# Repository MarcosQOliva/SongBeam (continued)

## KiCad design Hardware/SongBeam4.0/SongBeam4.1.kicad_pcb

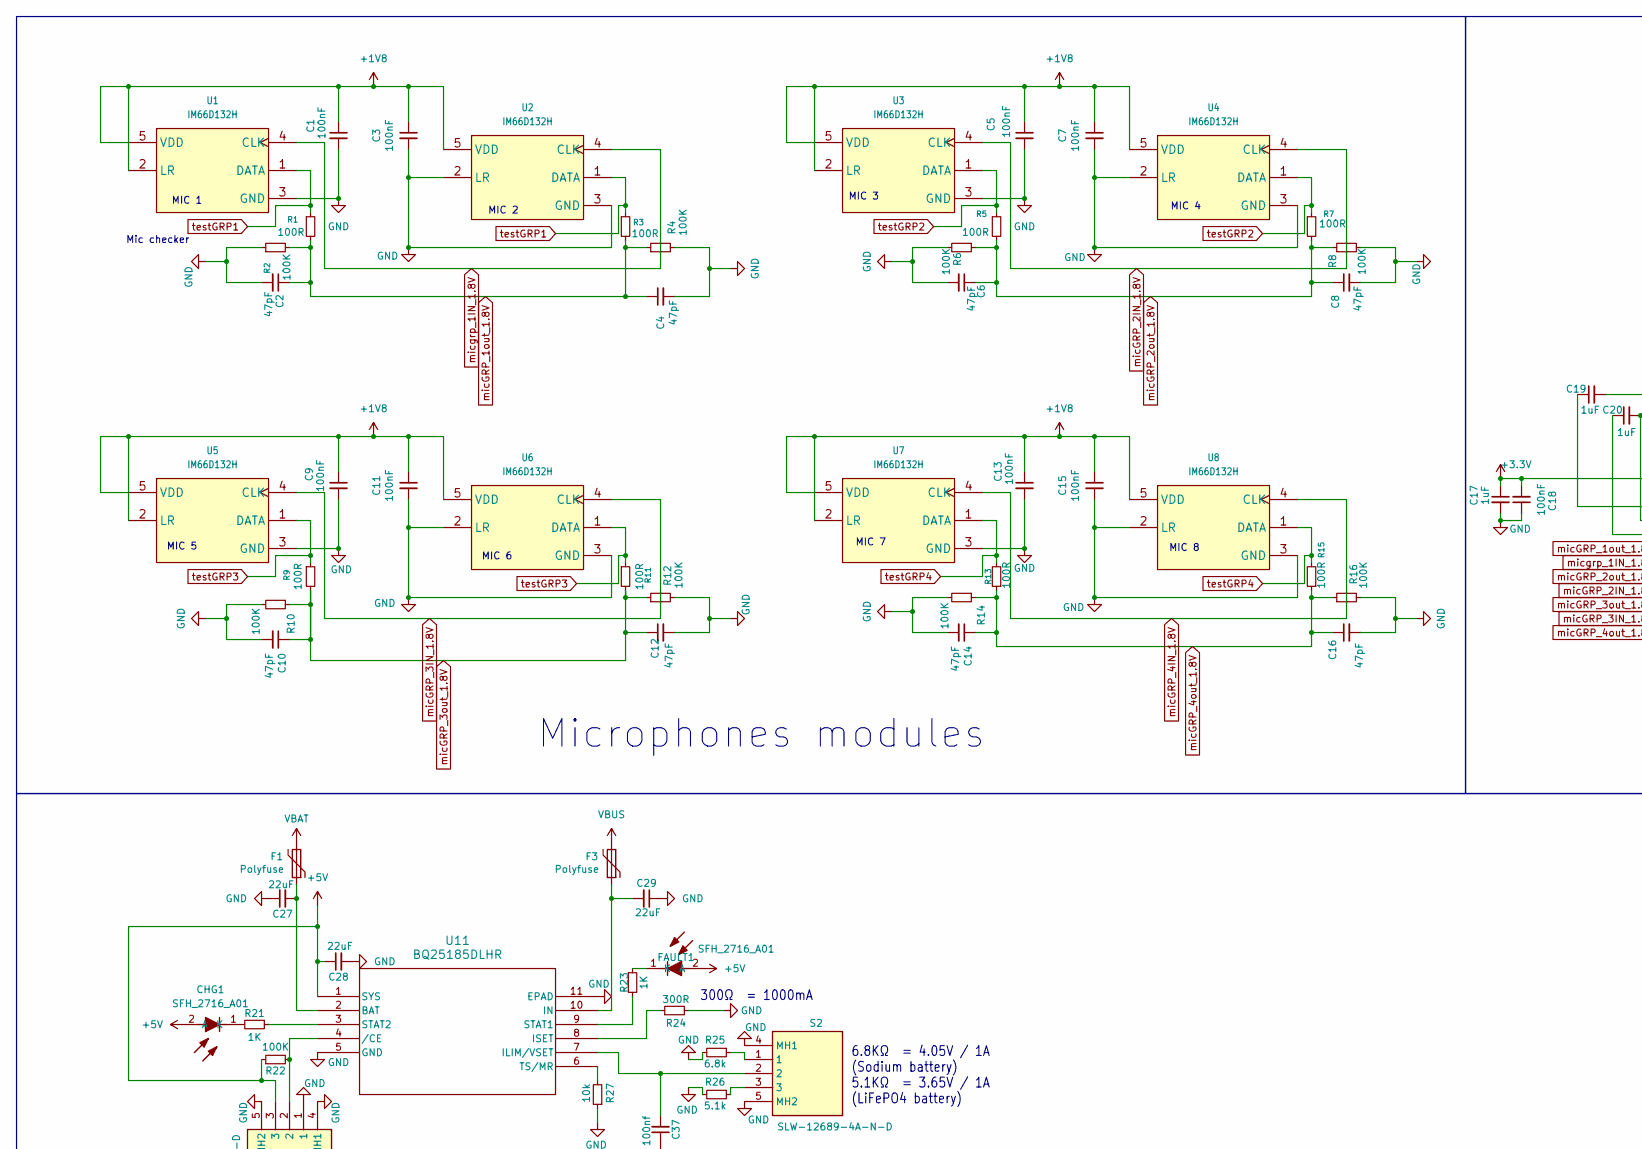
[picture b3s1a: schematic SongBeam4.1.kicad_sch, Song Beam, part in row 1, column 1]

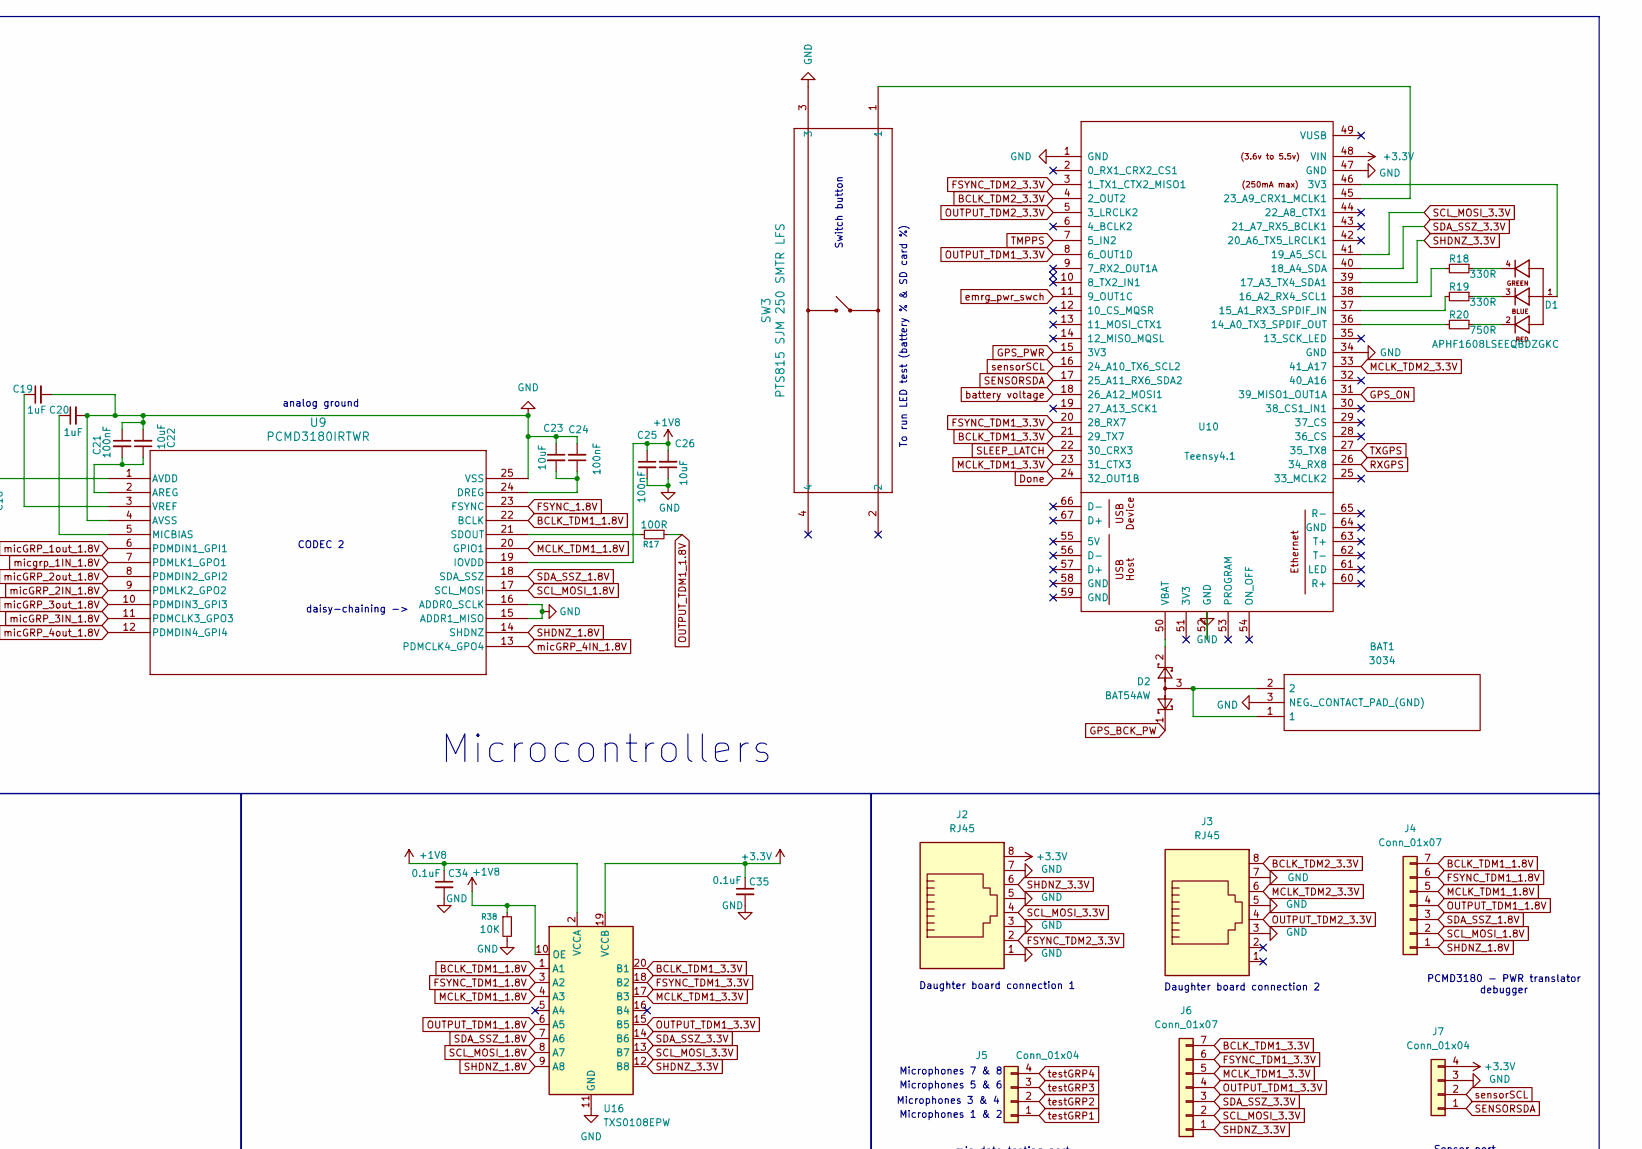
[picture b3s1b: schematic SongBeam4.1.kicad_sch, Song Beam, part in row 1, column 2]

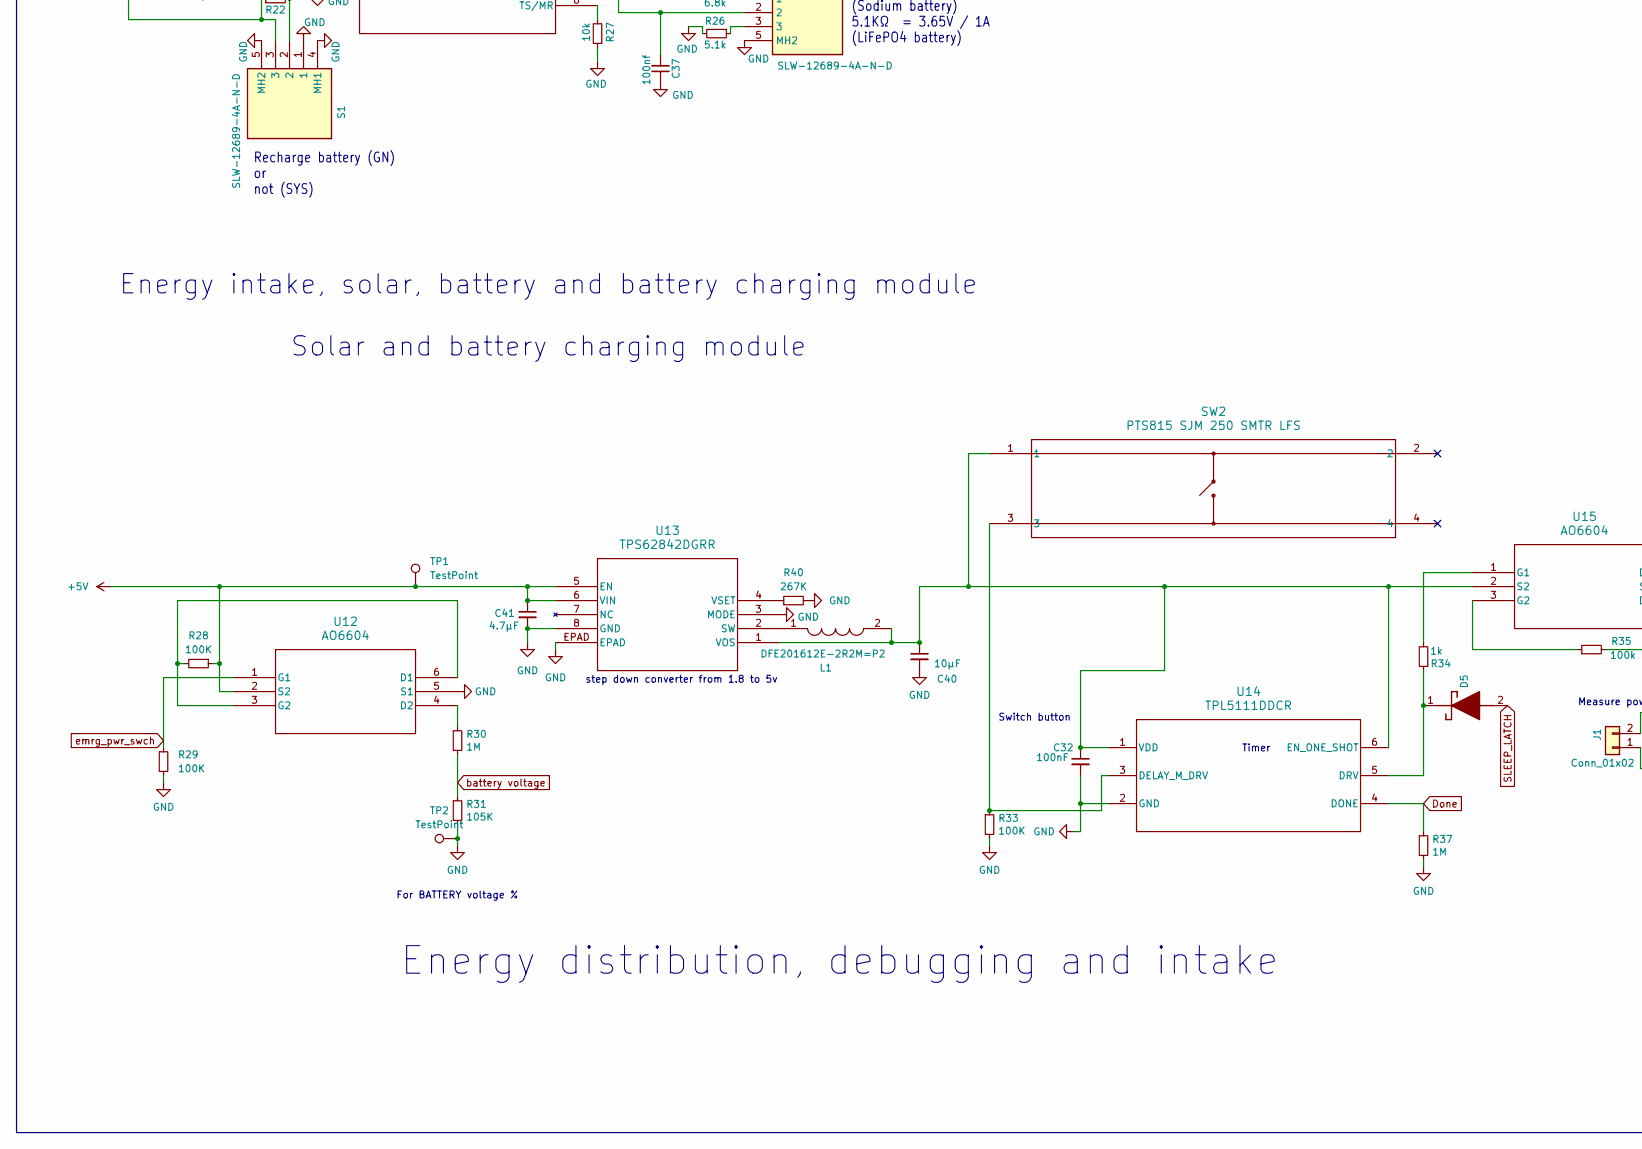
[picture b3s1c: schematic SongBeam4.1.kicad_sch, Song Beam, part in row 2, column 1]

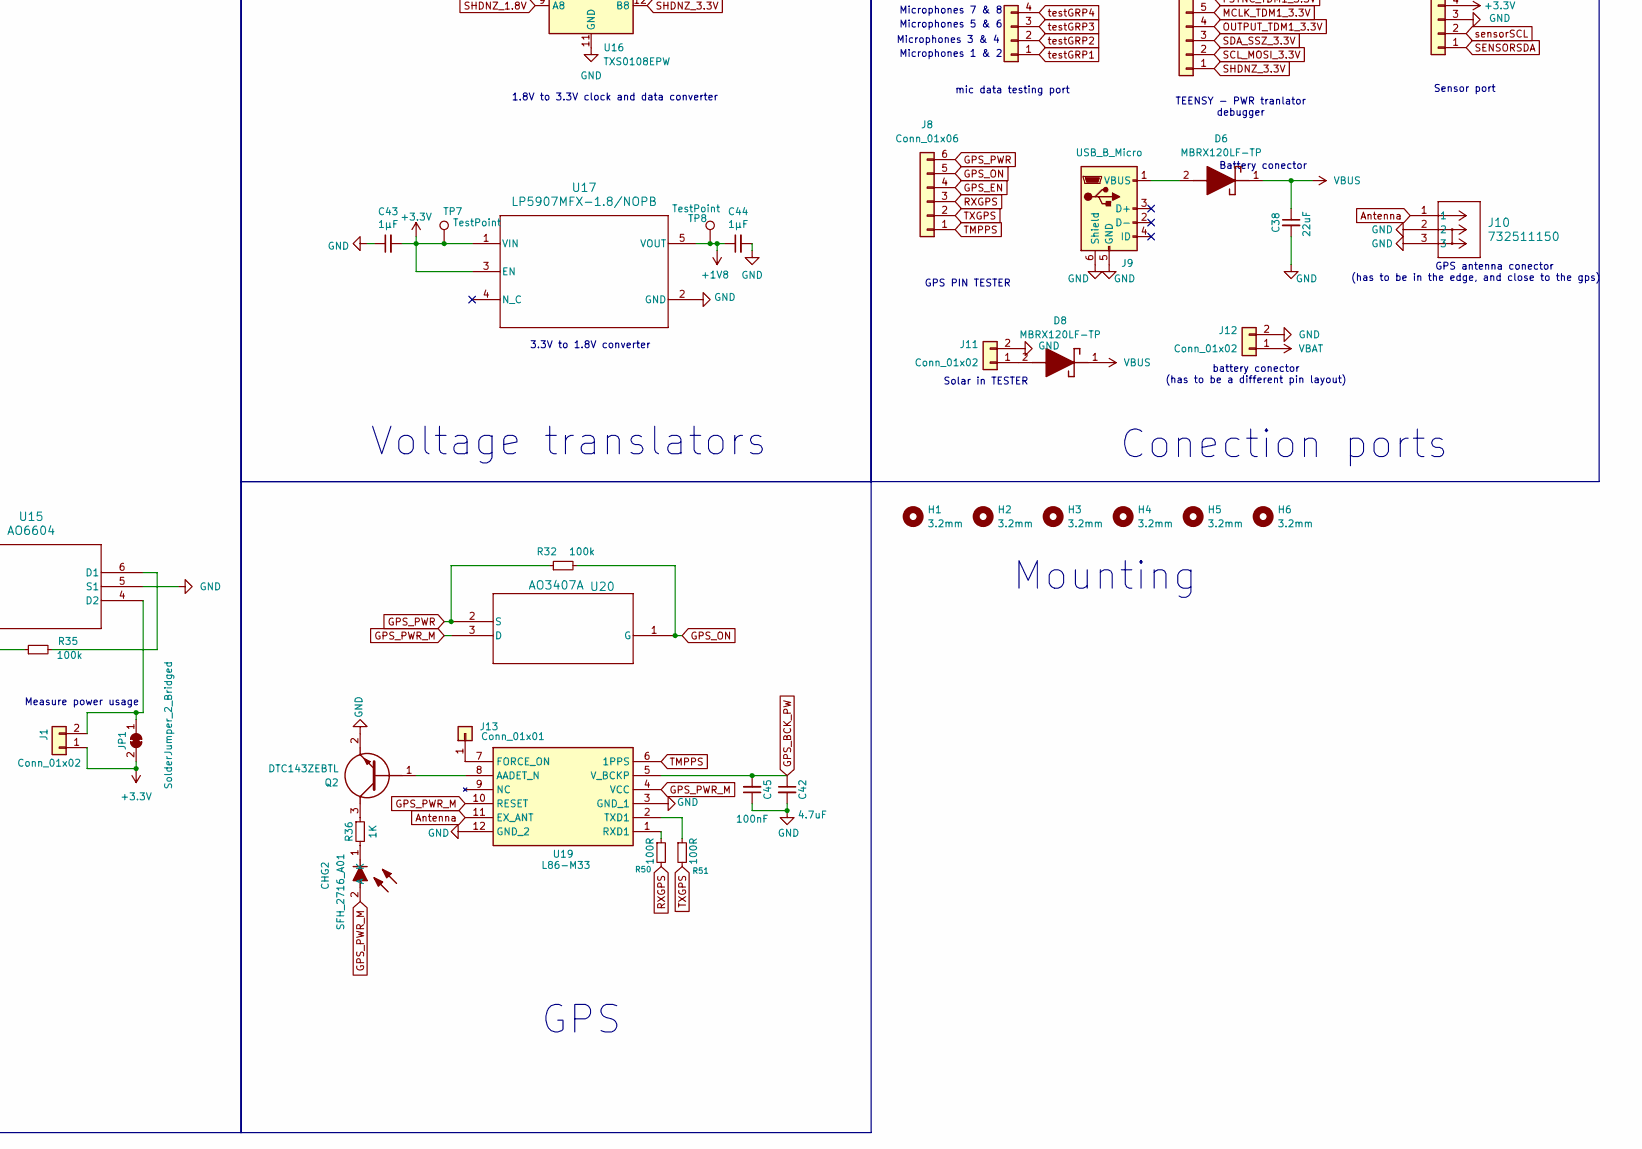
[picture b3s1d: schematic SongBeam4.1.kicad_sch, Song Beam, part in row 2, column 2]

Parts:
BAT1: 3034; 79523211; Manufacturer_Part_Number 3034; Mouser Part Number 534-3034
C1, C3, C5, C7, C9, C11, C13, C15, C18, C21, C24, C25, C32, C45: 100nF; C_0805_2012Metric
C2, C4, C6, C8, C10, C12, C14, C16: 47pF; C_0805_2012Metric
C17, C19, C20: 1uF; C_0805_2012Metric
C22, C23, C26: 10uF; C_0805_2012Metric
C27, C28, C29, C38: 22uF; C_0805_2012Metric
C34, C35: 0.1uF; C_0805_2012Metric
C37: 100nf; C_0805_2012Metric
C40: 10µF; C_0805_2012Metric
C41: 4.7µF; C_0805_2012Metric
C42: 4.7uF; C_0805_2012Metric
C43, C44: 1µF; C_0805_2012Metric
CHG1, CHG2: SFH_2716_A01; LEDC2012X100N; Mouser Part Number 720-SFH2716A01A0954
D1: APHF1608LSEEQBDZGKC; LED-APA102-2020; PARTREV V.3B; Mouser Part Number 604-APHF1608LQBDZGKC
D2: BAT54AW; SOT-323_SC-70
D5, D6, D8: MBRX120LF-TP; SOD3716X135N; Mouser Part Number 833-MBRX120LF-TP
F1, F3: Polyfuse; MINISMDC050F2
FAULT1: SFH_2716_A01; LEDC2012X100N; Mouser Part Number 720-SFH2716A01A0954
H1, H2, H3, H4, H5, H6: 3.2mm; MountingHole_3.2mm_M3_ISO14580
J1, J11, J12: Conn_01x02; PinHeader_1x02_P1.00mm_Vertical
J2, J3: RJ45; CONN_RJHSE-3380_AMP
J4, J6: Conn_01x07; PinHeader_1x07_P1.00mm_Vertical
J5, J7: Conn_01x04; PinHeader_1x04_P1.00mm_Vertical
J8: Conn_01x06; PinHeader_1x06_P1.00mm_Vertical
J9: USB_B_Micro; 101181920002LF
J10: 732511150; CONN_73251-1150_MOL
J13: Conn_01x01; PinHeader_1x01_P1.00mm_Vertical
JP1: SolderJumper_2_Bridged; SolderJumper-2_P1.3mm_Bridged_RoundedPad1.0x1.5mm
L1: DFE201612E-2R2M=P2; 1286ASH1R0MP2; Manufacturer_Part_Number DFE201612E-2R2M=P2; Mouser Part Number 81-DFE201612E-2R2MP2
Q2: DTC143ZEBTL; SOTFL50P160X85-3N; Mouser Part Number 755-DTC143ZEBTL
R1, R3, R5, R7, R9, R11, R13, R15, R17, R50, R51: 100R; R_0805_2012Metric
R2, R4, R6, R8, R10, R12, R14, R16, R22, R28, R29, R33: 100K; R_0805_2012Metric
R18, R19: 330R; R_0805_2012Metric
R20: 750R; R_0805_2012Metric
R21, R23, R36: 1K; R_0805_2012Metric
R24: 300R; R_0805_2012Metric
R25: 6.8k; R_0805_2012Metric
R26: 5.1k; R_0805_2012Metric
R27: 10k; R_0805_2012Metric
R30, R37: 1M; R_0805_2012Metric
R31: 105K; R_0805_2012Metric
R32, R35: 100k; R_0805_2012Metric
R34: 1k; R_0805_2012Metric
R38: 10K; R_0805_2012Metric
R40: 267K; R_0805_2012Metric
S1, S2: SLW-12689-4A-N-D; SLW126894AND; Mouser Part Number 179-SLW126894AND
SW2, SW3: PTS815 SJM 250 SMTR LFS; SW4_PTS815 SJM 250 SMTR LFS_CNK
TP1, TP2, TP7, TP8: TestPoint; TestPoint_Pad_D1.0mm
U1, U2, U3, U4, U5, U6, U7, U8: IM66D132H; IFX-PG-TLGA-5N-9-V
U9: PCMD3180IRTWR
U10: Teensy4.1; Teensy41
U11: BQ25185DLHR
U12, U15: AO6604
U13: TPS62842DGRR
U14: TPL5111DDCR; SOT95P280X110-6N
U16: TXS0108EPW; TSSOP-20_4.4x6.5mm_P0.65mm
U17: LP5907MFX-1.8/NOPB; DBV0005A_N
U19: L86-M33; L80-M39; Mouser Part Number 277-L86-M33
U20: AO3407A; SOT-23-3L_AOS

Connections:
+1V8: C1.1, C3.1, C5.1, C7.1, C9.1, C11.1, C13.1, C15.1, C25.1, C26.2, C34.1, C44.1, R38.1, TP8.1, U1.2 (LR), U1.5 (VDD), U2.5 (VDD), U3.2 (LR), U3.5 (VDD), U4.5 (VDD), U5.2 (LR), U5.5 (VDD), U6.5 (VDD), U7.2 (LR), U7.5 (VDD), U8.5 (VDD), U9.19 (IOVDD), U16.2 (VCCA), U16.10 (OE), U17.5 (VOUT)
+3.3V: C17.1, C18.2, C35.1, C43.2, J1.1, J2.8, J7.4, JP1.2 (B), TP7.1, U9.1 (AVDD), U10.48 (VIN), U16.19 (VCCB), U17.1 (VIN), U17.3 (EN)
+5V: C28.1, C41.1, CHG1.2 (A), FAULT1.2 (A), R22.1, R28.1, S1.3, TP1.1, U11.1 (SYS), U12.2 (S2), U13.5 (EN), U13.6 (VIN)
Antenna: J10.1, U19.11 (EX_ANT)
BCLK_TDM1_1.8V: J4.7, U9.22 (BCLK), U16.1 (A1)
BCLK_TDM1_3.3V: J6.7, U10.21 (29_TX7), U16.20 (B1)
BCLK_TDM2_3.3V: J3.8, U10.4 (2_OUT2)
Done: R37.1, U10.24 (32_OUT1B), U14.4 (DONE)
FSYNC_1.8V: U9.23 (FSYNC)
FSYNC_TDM1_1.8V: J4.6, U16.3 (A2)
FSYNC_TDM1_3.3V: J6.6, U10.20 (28_RX7), U16.18 (B2)
FSYNC_TDM2_3.3V: J2.2, U10.3 (1_TX1_CTX2_MISO1)
GND: BAT1.3 (NEG._CONTACT_PAD_(GND)), C1.2, C2.2, C3.2, C4.2, C5.2, C6.2, C7.2, C8.2, C9.2, C10.2, C11.2, C12.2, C13.2, C14.2, C15.2, C16.2, C17.2, C18.1, C19.2, C20.2, C21.1, C22.2, C23.1, C24.2, C25.2, C26.1, C27.1, C28.2, C29.1, C32.2, C34.2, C35.2, C37.1, C38.2, C40.2, C41.2, C42.2, C43.1, C44.2, C45.1, J2.1, J2.3, J2.5, J2.7, J3.3, J3.5, J3.7, J7.3, J9.5 (GND), J9.6 (Shield), J10.2, J10.3, J11.2, J12.2, Q2.2 (E), R2.1, R4.2, R6.2, R8.2, R10.2, R12.2, R14.2, R16.2, R24.2, R25.2, R26.2, R27.1, R29.2, R31.2, R33.2, R37.2, R38.2, R40.2, S1.1, S1.4 (MH1), S1.5 (MH2), S2.4 (MH1), S2.5 (MH2), SW3.3, TP2.1, U1.3 (GND), U2.2 (LR), U2.3 (GND), U3.3 (GND), U4.2 (LR), U4.3 (GND), U5.3 (GND), U6.2 (LR), U6.3 (GND), U7.3 (GND), U8.2 (LR), U8.3 (GND), U9.4 (AVSS), U9.15 (ADDR1_MISO), U9.16 (ADDR0_SCLK), U9.25 (VSS), U10.1 (GND), U10.34 (GND), U10.47 (GND), U10.52 (GND), U11.5 (GND), U11.11 (EPAD), U12.5 (S1), U13.3 (MODE), U13.8 (GND), U13.EPAD, U14.2 (GND), U15.5 (S1), U16.11 (GND), U17.2 (GND), U19.3 (GND_1), U19.12 (GND_2)
GPS_BCK_PW: C42.1, C45.2, D2.1, U19.5 (V_BCKP)
GPS_EN: J8.4
GPS_ON: J8.5, R32.2, U10.31 (39_MISO1_OUT1A), U20.1 (G)
GPS_PWR: J8.6, R32.1, U10.15 (3V3), U20.2 (S)
GPS_PWR_M: CHG2.2 (A), U19.4 (VCC), U19.10 (RESET), U20.3 (D)
MCLK_TDM1_1.8V: J4.5, U9.20 (GPIO1), U16.4 (A3)
MCLK_TDM1_3.3V: J6.5, U10.23 (31_CTX3), U16.17 (B3)
MCLK_TDM2_3.3V: J3.6, U10.33 (41_A17)
unnamed: BAT1.1, BAT1.2, D2.3
unnamed: CHG1.1 (K), R21.2
unnamed: CHG2.1 (K), R36.2
unnamed: D1.1, U10.46 (3V3)
unnamed: D1.2, R20.1
unnamed: D1.3, R19.1
unnamed: D1.4, R18.1
unnamed: D5.1 (K), R34.1, U14.5 (DRV)
unnamed: D6.2 (A), J9.1 (VBUS)
unnamed: D8.2 (A), J11.1
unnamed: FAULT1.1 (K), R23.1
unnamed: J1.2, JP1.1 (A), U15.4 (D2)
unnamed: J13.1, U19.7 (FORCE_ON)
unnamed: Q2.1 (B), U19.8 (AADET_N)
unnamed: Q2.3 (C), R36.1
unnamed: R25.1, S2.1
unnamed: R26.1, S2.3
unnamed: C21.2, C22.1, U9.2 (AREG)
unnamed: C23.2, C24.1, U9.24 (DREG)
unnamed: C20.1, U9.5 (MICBIAS)
unnamed: R17.2, U9.21 (SDOUT)
unnamed: C19.1, U9.3 (VREF)
unnamed: R20.2, U10.36 (14_A0_TX3_SPDIF_OUT)
unnamed: R19.2, U10.37 (15_A1_RX3_SPDIF_IN)
unnamed: R18.2, U10.38 (16_A2_RX4_SCL1)
unnamed: SW3.1, U10.45 (23_A9_CRX1_MCLK1)
unnamed: D2.2, U10.50 (VBAT)
unnamed: C27.2, F1.1, U11.2 (BAT)
unnamed: C37.2, S2.2, U11.7 (ILIM/VSET)
unnamed: C29.2, F3.1, U11.10 (IN)
unnamed: R24.1, U11.8 (ISET)
unnamed: R23.2, U11.9 (STAT1)
unnamed: R21.1, U11.3 (STAT2)
unnamed: R27.2, U11.6 (TS/MR)
unnamed: R22.2, S1.2, U11.4 (/CE)
unnamed: R28.2, U12.3 (G2), U12.6 (D1)
unnamed: R30.1, U12.4 (D2)
unnamed: L1.1, U13.2 (SW)
unnamed: C32.1, C40.1, L1.2, SW2.1, U13.1 (VOS), U14.1 (VDD), U14.6 (EN_ONE_SHOT), U15.2 (S2)
unnamed: R40.1, U13.4 (VSET)
unnamed: R33.1, SW2.3, U14.3 (DELAY_M_DRV)
unnamed: R35.2, U15.6 (D1)
unnamed: R34.2, U15.1 (G1)
unnamed: R35.1, U15.3 (G2)
unnamed: R50.1, U19.1 (RXD1)
unnamed: R51.1, U19.2 (TXD1)
OUTPUT_TDM1_1.8V: J4.4, R17.1, U16.6 (A5)
OUTPUT_TDM1_3.3V: J6.4, U10.8 (6_OUT1D), U16.15 (B5)
OUTPUT_TDM2_3.3V: J3.4, U10.5 (3_LRCLK2)
RXGPS: J8.3, R50.2, U10.26 (34_RX8)
SCL_MOSI_1.8V: J4.2, U9.17 (SCL_MOSI), U16.8 (A7)
SCL_MOSI_3.3V: J2.4, J6.2, U10.41 (19_A5_SCL), U16.13 (B7)
SDA_SSZ_1.8V: J4.3, U9.18 (SDA_SSZ), U16.7 (A6)
SDA_SSZ_3.3V: J6.3, U10.40 (18_A4_SDA), U16.14 (B6)
SENSORSDA: J7.1, U10.17 (25_A11_RX6_SDA2)
SHDNZ_1.8V: J4.1, U9.14 (SHDNZ), U16.9 (A8)
SHDNZ_3.3V: J2.6, J6.1, U10.39 (17_A3_TX4_SDA1), U16.12 (B8)
SLEEP_LATCH: D5.2 (A), U10.22 (30_CRX3)
TMPPS: J8.1, U10.7 (5_IN2), U19.6 (1PPS)
TXGPS: J8.2, R51.2, U10.27 (35_TX8)
VBAT: F1.2, J12.1
VBUS: C38.1, D6.1 (K), D8.1 (K), F3.2
battery voltage: R30.2, R31.1, U10.18 (26_A12_MOSI1)
emrg_pwr_swch: R29.1, U10.11 (9_OUT1C), U12.1 (G1)
micGRP_1out_1.8V: C2.1, C4.1, R1.2, R2.2, R3.2, R4.1, U9.6 (PDMDIN1_GPI1)
micGRP_2IN_1.8V: U3.4 (CLK), U4.4 (CLK), U9.9 (PDMLK2_GPO2)
micGRP_2out_1.8V: C6.1, C8.1, R5.2, R6.1, R7.2, R8.1, U9.8 (PDMDIN2_GPI2)
micGRP_3IN_1.8V: U5.4 (CLK), U6.4 (CLK), U9.11 (PDMCLK3_GPO3)
micGRP_3out_1.8V: C10.1, C12.1, R9.2, R10.1, R11.2, R12.1, U9.10 (PDMDIN3_GPI3)
micGRP_4IN_1.8V: U7.4 (CLK), U8.4 (CLK), U9.13 (PDMCLK4_GPO4)
micGRP_4out_1.8V: C14.1, C16.1, R13.1, R14.1, R15.1, R16.1, U9.12 (PDMDIN4_GPI4)
micgrp_1IN_1.8V: U1.4 (CLK), U2.4 (CLK), U9.7 (PDMLK1_GPO1)
sensorSCL: J7.2, U10.16 (24_A10_TX6_SCL2)
testGRP1: J5.1, R1.1, R3.1, U1.1 (DATA), U2.1 (DATA)
testGRP2: J5.2, R5.1, R7.1, U3.1 (DATA), U4.1 (DATA)
testGRP3: J5.3, R9.1, R11.1, U5.1 (DATA), U6.1 (DATA)
testGRP4: J5.4, R13.2, R15.2, U7.1 (DATA), U8.1 (DATA)

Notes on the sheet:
PCMD3180 - PWR translator debugger
Sensor port
battery conector (has to be a different pin layout)
Microphones modules
Switch button
Recharge battery (GN) or not (SYS)
Solar in TESTER
step down converter from 1.8 to 5v
Microphones 7 & 8
Energy intake, solar, battery and battery charging module Solar and battery charging module
GPS PIN TESTER
6.8KΩ = 4.05V / 1A (Sodium battery) 5.1KΩ = 3.65V / 1A (LiFePO4 battery)
Daughter board connection 1
Conection ports
MIC 6
MIC 4
To run LED test (battery % & SD card %)
3.3V to 1.8V converter
MIC 7
analog ground
300Ω = 1000mA
Daughter board connection 2
Mounting
Voltage translators
Battery conector
MIC 3
MIC 8
MIC 5
Timer
Microphones 1 & 2
Microphones 5 & 6
1.8V to 3.3V clock and data converter
Microphones 3 & 4
Microcontrollers
Energy distribution, debugging and intake
daisy-chaining ->
For BATTERY voltage %
MIC 2
MIC 1
CODEC 2

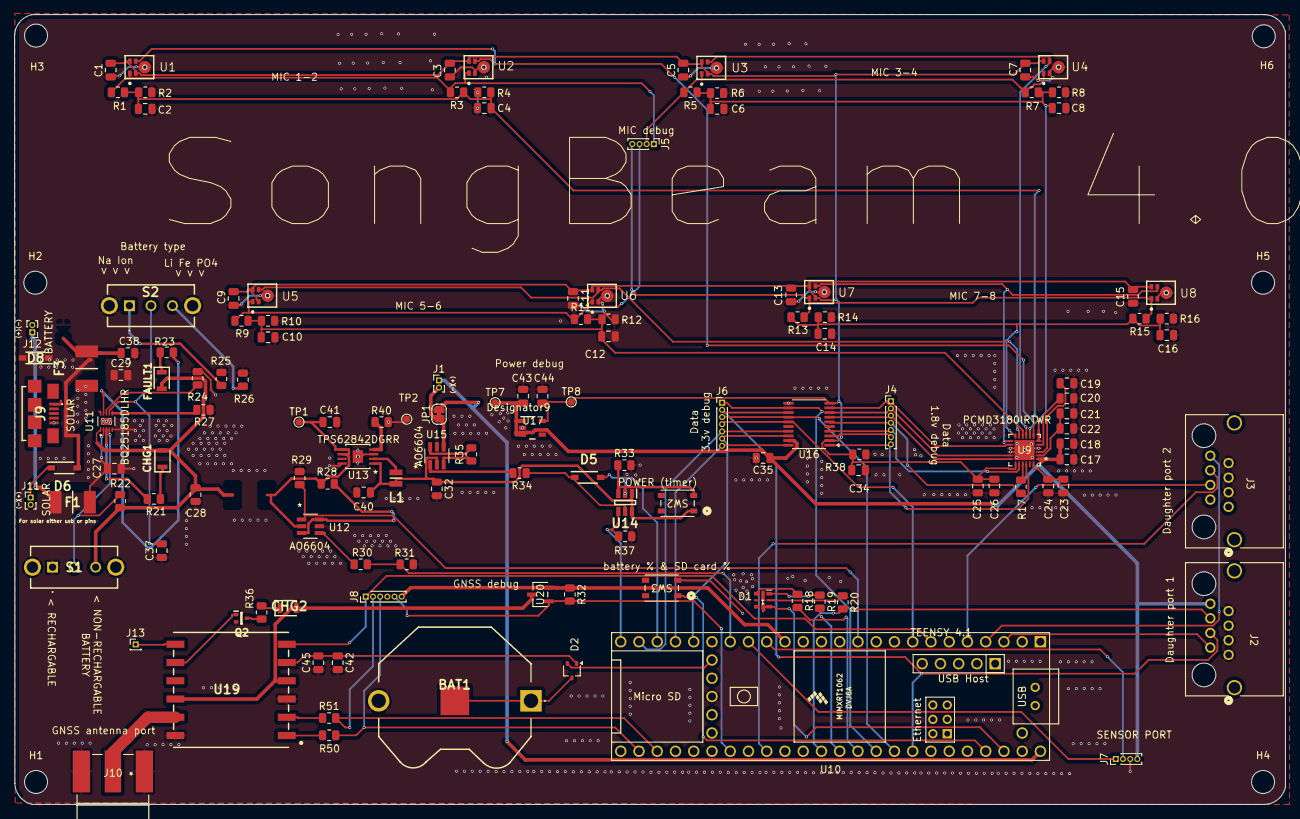
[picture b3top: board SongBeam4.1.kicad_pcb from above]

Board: 2 copper layers, 176.9 x 110.0 mm, 141 parts (0 on the bottom side), 94 nets.

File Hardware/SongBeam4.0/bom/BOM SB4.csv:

Designator,Value,Footprint,Quantity, Manufacturer_Name, Manufacturer_Part_Number,Supplier part number,Supplier,Annotation
"C1, C3, C5, C7, C9, C13, C15, C18, C21, C24, C25, C32, C34, C35, C37, C45",100nF,C_0805_2012Metric,17,,,0805-100nF-50V,PCBTrain,Newbury free stock
"C2, C4, C6, C8, C10, C14, C16",47pF,C_0805_2012Metric,8,,,0805-47pF-50V,PCBTrain,Newbury free stock
"C17, C19, C20, C43, C44",1µF,C_0805_2012Metric,4,,,0805-1uF-25V,PCBTrain,Newbury free stock
"C22, C23, C26, C40",10uF,C_0805_2012Metric,4,,,0805-10uF-16V,PCBTrain,Newbury free stock
"C27, C28, C29, C38",22uF,C_0805_2012Metric,4,,,0805-22uF-16V,PCBTrain,Newbury free stock
"C41, C42",4.7µF,C_0805_2012Metric,2,,,0805-4.7uF-25V,PCBTrain,Newbury free stock
"R2, R4, R6, R8, R10, R12, R14, R16, R22, R28, R29, R32, R33, R35",100K,R_0805_2012Metric,14,,,0805-100K,PCBTrain,Newbury free stock
"R1, R3, R5, R7, R9, R13, R15, R17, R50, R51",100R,R_0805_2012Metric,10,,,0805-100R,PCBTrain,Newbury free stock
"R21, R23, R34, R36",1K,R_0805_2012Metric,4,,,0805-1K,PCBTrain,Newbury free stock
"R18, R19",330R,R_0805_2012Metric,2,,,0805-330R,PCBTrain,Newbury free stock
"R27, R38",10K,R_0805_2012Metric,2,,,0805-10K,PCBTrain,Newbury free stock
"R30, R37",1M,R_0805_2012Metric,2,,,0805-1M,PCBTrain,Newbury free stock
R20,750R,R_0805_2012Metric,1,,,0805-750R,PCBTrain,Newbury free stock
R24,300R,R_0805_2012Metric,1,,,0805-300,PCBTrain,Newbury free stock
R25,6.8k,R_0805_2012Metric,1,Vishay,TNPW06036K80BEEA,71-TNPW06036K80BEEA,Mouser,
R26,5.1k,R_0805_2012Metric,1,Vishay,TNPW08055K10BEEN,71-TNPW08055K10BEEN,Mouser,
R31,105K,R_0805_2012Metric,1,Vishay,CRCW0805105KFKEAC,71-CRCW0805105KFKEAC,Mouser,
R40,267K,R_0805_2012Metric,1,Vishay,CRCW0805267KFKEA,71-CRCW0805267KFKEA,Mouser,
L1,DFE201612E-2R2M=P2,1286ASH1R0MP2,1, Murata Electronics,DFE201612E-2R2M=P2,81-DFE201612E-2R2MP2,Mouser,
"D5, D6,D8",MBRX120LF-TP,SOD3716X135N,3,Micro Commercial Components (MCC) ,MBRX120LF-TP,833-MBRX120LF-TP,Mouser,
D1,APHF1608LSEEQBDZGKC,LED-APA102-2020,1,Kingbright ,APHF1608LSEEQBDZGKC,604-APHF1608LQBDZGKC,Mouser,
D2,BAT54AW,SOT-323_SC-70,1,Diotec Semiconductor ,BAT54AW,637-BAT54AW,Mouser,
"U1, U2, U3, U4, U5, U7, U8",IM66D132H,IFX-PG-TLGA-5N-9-V,8,Infineon Technologies ,IM66D132HV01XTMA1,726-IM66D132HV01XTMA,Mouser,
"U12, U15",AO6604,AO6604,2,Alpha & Omega Semiconductor Inc.,AO6604,AO6604,Digikey,
U9,PCMD3180IRTWR,PCMD3180IRTWR,1,Texas Instruments,PCMD3180IRTWR,595-PCMD3180IRTWR,Mouser,
U11,BQ25185DLHR,BQ25185DLHR,1,Texas Instruments,BQ25185DLHR,595-BQ25185DLHR,Mouser,
U13,TPS62842DGRR,TPS62842DGRR,1,Texas Instruments,TPS62842DGRR,595-TPS62842DGRR,Mouser,
U14,TPL5111DDCR,SOT95P280X110-6N,1,Texas Instruments,TPL5111DDCR,595-TPL5111DDCR,Mouser,
U16,TXS0108EPW,TSSOP-20_4.4x6.5mm_P0.65mm,1,Texas Instruments,TXS0108EPWR,595-TXS0108EPWR,Mouser,
U17,LP5907MFX-1.8/NOPB,DBV0005A_N,1,Texas Instruments,LP5907MFX-1.8/NOPB,595-LP5907MFX-1.8NPB,Mouser,
U19,L86-M33,L80-M39,1,Quectel,L86-M33,277-L86-M33,Mouser,
U20,AO3407A,SOT-23-3L_AOS,1,Infineon Technologies ,IRLML9301TRPBF,942-IRLML9301TRPBF,Mouser,
"F3,F1",Polyfuse,MINISMDC050F2,2,Littelfuse ,MINISMDC050F-2,650-MINISMDC050F-2,Mouser,
"SW2, SW3",PTS815 SJM 250 SMTR LFS,SW4_PTS815 SJM 250 SMTR LFS_CNK,2,C&K ,PTS815SJM250SMTR LFS,611-PTS815SJM250SMTR,Mouser,
"ANT_DBG, CHG1, FAULT1",SFH_2716_A01,LEDC2012X100N,3,ams OSRAM ,SFH 2716 A01,720-SFH2716A01A0954,Mouser,
"S1, S2",SLW-12689-4A-N-D,SLW126894AND,2,Same Sky ,SLW-12689-4A-N-D,179-SLW126894AND,Mouser,
BAT1,3034,79523211,1,Wurth Elektronik,79523211,710-79523211,Mouser,
Q2,DTC143ZEBTL,SOTFL50P160X85-3N,1,ROHM Semiconductor,DTC143ZEBTL,755-DTC143ZEBTL,Mouser,
"J2, J3",RJ45,CONN_RJHSE-3380_AMP,2,Amphenol Commercial Products ,RJHSE3380A1,523-RJHSE3380A1,Mouser,
J9,USB_B_Micro,101181920002LF,1,Amphenol FCI,10118192-0002LF,649-10118192-0002LF,Mouser,
J10,732511150,CONN_73251-1150_MOL,1,Molex,73251-1150,538-73251-1150,Mouser,

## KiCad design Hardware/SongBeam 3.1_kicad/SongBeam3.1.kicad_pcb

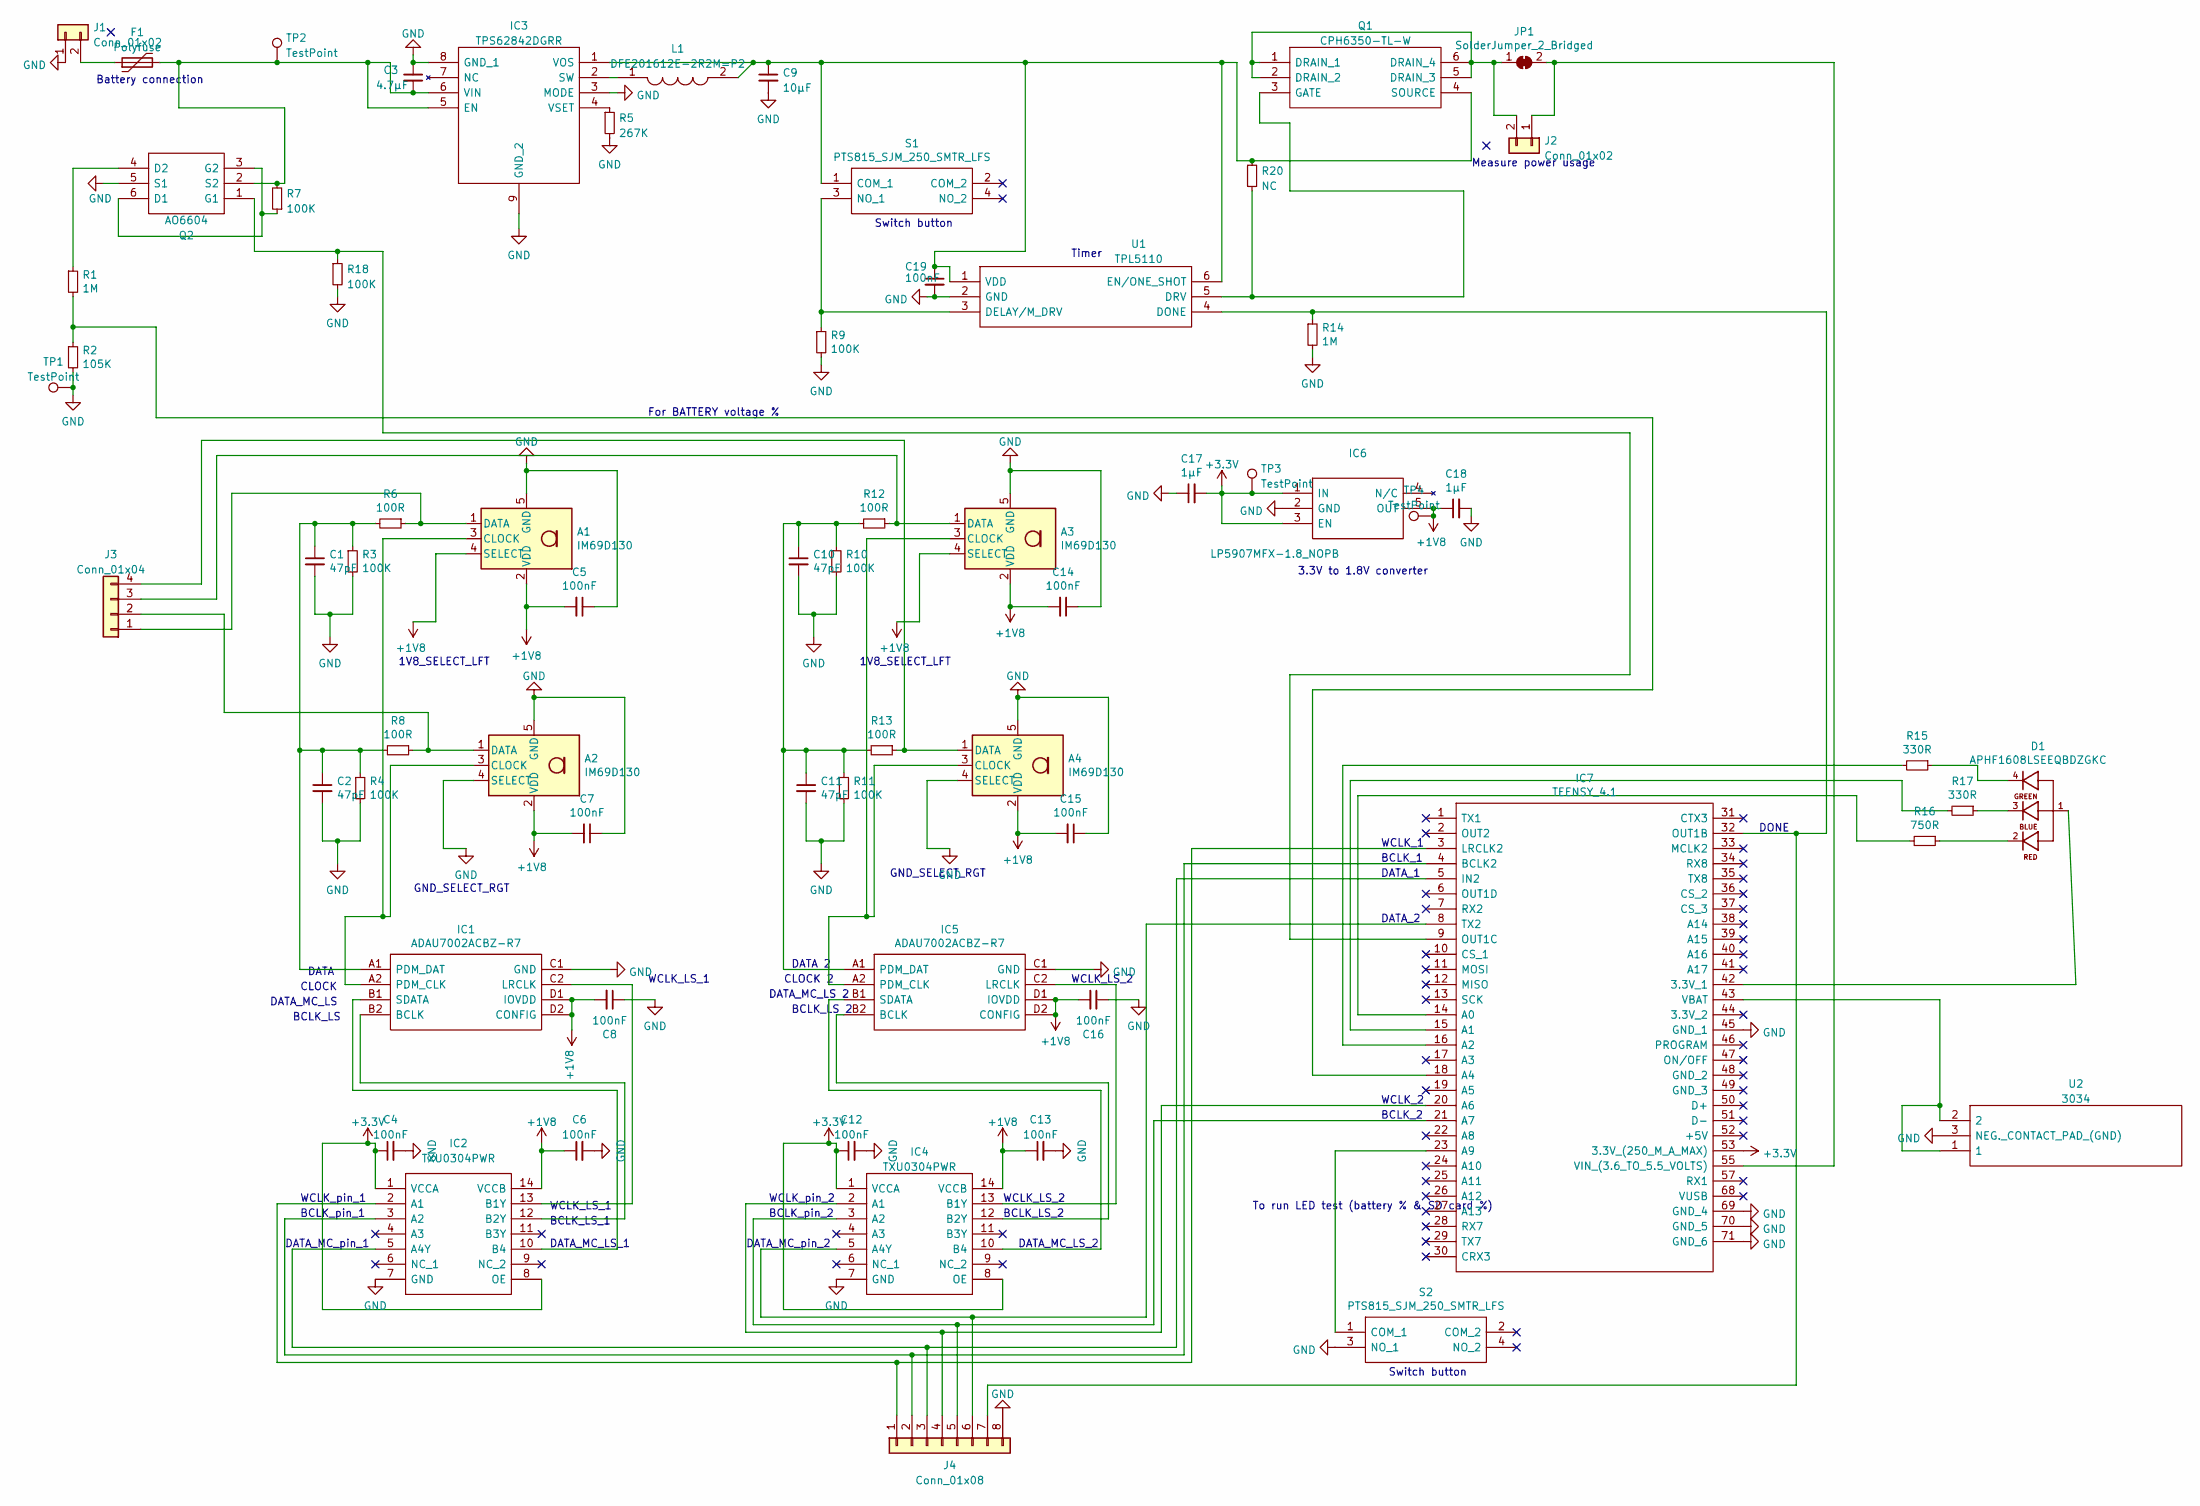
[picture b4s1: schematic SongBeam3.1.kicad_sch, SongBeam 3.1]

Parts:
A1, A2, A3, A4: IM69D130; Infineon_PG-LLGA-5-1; Manufacturer_Part_Number IM69D130V01XTSA1; Mouser Part Number 726-IM69D130V01XTSA1
C1, C2, C10, C11: 47pF; C_0805_2012Metric
C3: 4.7µF; C_0805_2012Metric
C4, C5, C6, C7, C8, C12, C13, C14, C15, C16, C19: 100nF; C_0805_2012Metric
C9: 10µF; C_0805_2012Metric
C17, C18: 1µF; C_0805_2012Metric
D1: APHF1608LSEEQBDZGKC; LED_APHF1608LSEEQBDZGKC; PARTREV V.3B; Mouser Part Number 604-APHF1608LQBDZGKC
F1: Polyfuse; MINISMDC050F2
IC1, IC5: ADAU7002ACBZ-R7; BGA8C40P2X4_76X156X56; Manufacturer_Part_Number ADAU7002ACBZ-R7; Mouser Part Number 584-ADAU7002ACBZ-R7
IC2, IC4: TXU0304PWR; SOP65P640X120-14N; Manufacturer_Part_Number TXU0304PWR; Mouser Part Number 595-TXU0304PWR
IC3: TPS62842DGRR; SOP65P490X110-9N; Manufacturer_Part_Number TPS62842DGRR; Mouser Part Number 595-TPS62842DGRR
IC6: LP5907MFX-1.8_NOPB; SOT95P280X145-5N; Manufacturer_Part_Number LP5907MFX-1.8/NOPB; Mouser Part Number 595-LP5907MFX-1.8NPB
IC7: TEENSY_4.1; TEENSY41; Manufacturer_Part_Number TEENSY 4.1
J1: Conn_01x02; SolderWire_1x02_P2.52
J2: Conn_01x02; PinSocket_1x02_P2.54mm_Vertical
J3: Conn_01x04; PinSocket_1x04_P2.54mm_Vertical
J4: Conn_01x08; PinSocket_1x08_P2.54mm_Vertical
JP1: SolderJumper_2_Bridged; SolderJumper-2_P1.3mm_Bridged_RoundedPad1.0x1.5mm
L1: DFE201612E-2R2M=P2; 1286ASH1R0MP2; Manufacturer_Part_Number DFE201612E-2R2M=P2; Mouser Part Number 81-DFE201612E-2R2MP2
Q1: CPH6350-TL-W; SOT95P280X105-6N; Manufacturer_Part_Number CPH6350-TL-W; Mouser Part Number 863-CPH6350-TL-W
Q2: AO6604; TSOP-6_1.65x3.05mm_P0.95mm; Manufacturer_Part_Number AO6604
R1, R14: 1M; R_0805_2012Metric
R2: 105K; R_0805_2012Metric
R3, R4, R7, R9, R10, R11, R18: 100K; R_0805_2012Metric
R5: 267K; R_0805_2012Metric
R6, R8, R12, R13: 100R; R_0805_2012Metric
R15, R17: 330R; R_0805_2012Metric
R16: 750R; R_0805_2012Metric
R20: NC; R_0805_2012Metric
S1, S2: PTS815_SJM_250_SMTR_LFS; PTS815SJM250SMTRLFS; Manufacturer_Part_Number PTS815 SJM 250 SMTR LFS; Mouser Part Number 611-PTS815SJM250SMTR
TP1, TP2, TP3, TP4: TestPoint; TestPoint_Pad_D1.0mm
U1: TPL5110; SOT95P280X110-6N; Manufacturer_Part_Number TPL5110DDCR; Mouser Part Number 595-TPL5110DDCR
U2: 3034; BatteryHolder_Keystone_3034_1x20mm; Manufacturer_Part_Number 3034; Mouser Part Number 534-3034

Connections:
+1V8: A1.2 (VDD), A1.4 (SELECT), A2.2 (VDD), A3.2 (VDD), A3.4 (SELECT), A4.2 (VDD), C5.2, C6.1, C7.2, C8.2, C13.1, C14.2, C15.2, C16.2, C18.1, IC1.D1 (IOVDD), IC1.D2 (CONFIG), IC2.14 (VCCB), IC4.14 (VCCB), IC5.D1 (IOVDD), IC5.D2 (CONFIG), IC6.5 (OUT), TP4.1
+3.3V: C4.1, C12.1, C17.2, IC2.1 (VCCA), IC2.8 (OE), IC4.1 (VCCA), IC4.8 (OE), IC6.1 (IN), IC6.3 (EN), IC7.53 (3.3V_(250_M_A_MAX)), TP3.1
GND: A1.5 (GND), A2.4 (SELECT), A2.5 (GND), A3.5 (GND), A4.4 (SELECT), A4.5 (GND), C1.2, C2.2, C3.1, C4.2, C5.1, C6.2, C7.1, C8.1, C9.2, C10.2, C11.2, C12.2, C13.2, C14.1, C15.1, C16.1, C17.1, C18.2, C19.2, IC1.C1 (GND), IC2.7 (GND), IC3.3 (MODE), IC3.8 (GND_1), IC3.9 (GND_2), IC4.7 (GND), IC5.C1 (GND), IC6.2 (GND), IC7.45 (GND_1), IC7.69 (GND_4), IC7.70 (GND_5), IC7.71 (GND_6), J1.1, J4.8, Q2.5 (S1), R2.2, R3.2, R4.2, R5.2, R9.2, R10.2, R11.2, R14.2, R18.2, S2.3 (NO_1), TP1.1, U1.2 (GND), U2.3 (NEG._CONTACT_PAD_(GND))
unnamed: A1.1 (DATA), J3.1, R6.1
unnamed: A1.3 (CLOCK), A2.3 (CLOCK), IC1.A2 (PDM_CLK)
unnamed: A2.1 (DATA), J3.2, R8.1
unnamed: A3.1 (DATA), J3.3, R12.1
unnamed: A3.3 (CLOCK), A4.3 (CLOCK), IC5.A2 (PDM_CLK)
unnamed: A4.1 (DATA), J3.4, R13.1
unnamed: C1.1, C2.1, IC1.A1 (PDM_DAT), R3.1, R4.1, R6.2, R8.2
unnamed: C3.2, F1.2, IC3.5 (EN), IC3.6 (VIN), Q2.2 (S2), R7.2, TP2.1
unnamed: C10.1, C11.1, IC5.A1 (PDM_DAT), R10.1, R11.1, R12.2, R13.2
unnamed: C9.1, C19.1, IC3.1 (VOS), L1.2, Q1.4 (SOURCE), R20.1, S1.1 (COM_1), U1.1 (VDD), U1.6 (EN/ONE_SHOT)
unnamed: D1.1, IC7.42 (3.3V_1)
unnamed: D1.2, R16.1
unnamed: D1.3, R17.1
unnamed: D1.4, R15.1
unnamed: F1.1, J1.2
unnamed: IC1.B1 (SDATA), IC2.10 (B4)
unnamed: IC1.B2 (BCLK), IC2.12 (B2Y)
unnamed: IC1.C2 (LRCLK), IC2.13 (B1Y)
unnamed: IC2.2 (A1), IC7.3 (LRCLK2), J4.1
unnamed: IC2.3 (A2), IC7.4 (BCLK2), J4.2
unnamed: IC2.5 (A4Y), IC7.5 (IN2), J4.3
unnamed: IC3.2 (SW), L1.1
unnamed: IC3.4 (VSET), R5.1
unnamed: IC4.2 (A1), IC7.20 (A6), J4.4
unnamed: IC4.3 (A2), IC7.21 (A7), J4.5
unnamed: IC4.5 (A4Y), IC7.8 (TX2), J4.6
unnamed: IC4.10 (B4), IC5.B1 (SDATA)
unnamed: IC4.12 (B2Y), IC5.B2 (BCLK)
unnamed: IC4.13 (B1Y), IC5.C2 (LRCLK)
unnamed: IC7.9 (OUT1C), Q2.1 (G1), R18.1
unnamed: IC7.14 (A0), R16.2
unnamed: IC7.15 (A1), R17.2
unnamed: IC7.16 (A2), R15.2
unnamed: IC7.18 (A4), R1.2, R2.1
unnamed: IC7.23 (A9), S2.1 (COM_1)
unnamed: IC7.32 (OUT1B), J4.7, R14.1, U1.4 (DONE)
unnamed: IC7.43 (VBAT), U2.1, U2.2
unnamed: IC7.55 (VIN_(3.6_TO_5.5_VOLTS)), J2.1, JP1.2 (B)
unnamed: J2.2, JP1.1 (A), Q1.1 (DRAIN_1), Q1.2 (DRAIN_2), Q1.5 (DRAIN_3), Q1.6 (DRAIN_4)
unnamed: Q1.3 (GATE), R20.2, U1.5 (DRV)
unnamed: Q2.3 (G2), Q2.6 (D1), R7.1
unnamed: Q2.4 (D2), R1.1
unnamed: R9.1, S1.3 (NO_1), U1.3 (DELAY/M_DRV)

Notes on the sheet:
BCLK_LS
DATA_MC_LS 2
DATA_MC_LS_2
WCLK_LS_1
Switch button
WCLK_pin_1
BCLK_LS_2
CLOCK 2
DATA_MC_LS
Battery connection
CLOCK
WCLK_2
BCLK_pin_1
WCLK_LS_2
3.3V to 1.8V converter
GND_SELECT_RGT
DATA 2
WCLK_1
BCLK_2
1V8_SELECT_LFT
To run LED test (battery % & SD card %)
DATA_MC_pin_1
BCLK_1
For BATTERY voltage %
BCLK_LS_1
WCLK_pin_2
DATA
Measure power usage
DATA_MC_LS_1
BCLK_LS 2
DATA_MC_pin_2
DONE
DATA_1
BCLK_pin_2
Timer
DATA_2
